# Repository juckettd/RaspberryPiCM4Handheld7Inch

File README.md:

# Raspberry Pi CM4 Handheld 7 - Aegis"

<p align="center"></p>

A repository for the Aegis, a 7" Raspberry Pi CM4 handheld device.

NOTE: This is still a work in progress. The design has been finalized but I'm still working on the instructions, therefore there might be steps that are missing at this moment.

## Summary

The Aegis is a DIY handheld that uses a 3D printed case with a Raspberry Pi CM4 and the official Raspberry Pi 7" screen. The official Raspberry Pi screen was chosen because it uses the DSI port on the Raspberry Pi and the CM4 could fit on either side of the display board. While a Raspberry Pi 4 might have fit inside the case, that was eventually designed, a custom carrier board was used to place the ports in the desired locations. To facilitate the controller portion of the device, the Wii U buttons and joysticks were used. This made it easy to use the button sub-assemblies so that the same tactile feel of the buttons could be maintained. The 3D printed case was based on the Wii U Gamepad but still designed from the ground up to fit the 7" screen and the custom circuit board. Finally, the whole thing was assembled with speakers and rumble motors to complete the handheld.

## Building the Handheld

To build the handheld you will need the items listed as required in the Bill of Materials along with the following tools:

Reflow Station or Reflow Oven<br/>
Solding Iron<br/>
Solder Paste<br/>
Tweezers<br/>
Small Philips Screw Driver<br/>
Small Flathead Screw Driver<br/>
Super Glue (preferrably CA glue with Accelerator)

There are items in the Bill of Materials that are listed as optional (such as the Wifi chip). These items are not required to get a working device but can be used if desired. At this time I will not provide directions on how to use the optional components so use at your discretion.

### Assembling the Circuit Board

The custom circuit boards are provided as eagle files in this repository. This includes the schematic, board layout, and the gerber files. 

To get the boards printed, a manufacturing facility is required. The website jlcpcb.com was used to print the 2 circuit board prototypes for the design. The larger of the two boards uses 4 layers, and the smaller one uses only 2 layers. It is recommended to also get the stencils with the boards so that applying the solder paste becomes much easier.

Once the boards have been received you will need to assemble the circuitry on the boards. This is done by getting all of the components provided in the bill of materials in the "PCB Components" sheet. Each item has a provided Link to where the item can be acquired along with the price at the time of the assembly of the prototype. After acquiring all of the components, use the stencil to apply solder paste to the circuit boards and then use tweezers to place each component. A reflow oven or reflow station should then be used to melt the solder paste and adhere the components. Lastly, any through hole components were then added on the using a soldering iron. 

Note: The teensy that is soldered to the board using the through holes. However, there are 4 pads that are located near the USB connector of the Teensy on the custom circuit board. They are the VBUS, D+, D-, and GND connections. I included the VBUS and GND connections as backups but they are not needed as the power and ground comes from the pins. But the D+, D- connections need to be connected to the teensy. On the underside of the teensy there are 4 pads that are in about the same location, a wire or some other form of connection is needed to connect the D+ from the teensy to the D+ on the custom circuit board, do the same with the D- connection.

While anyone who has experience with circuit boards will have their own method for assembling these boards I used the following steps and it is what I recommend for anyone without experience and a reflow oven (but a reflow station is required):
1. Using the stencil, put solder paste on the larger of the two boards on the side with a majority of the components
2. Place all of the surface mount components on that side of the board
3. Use a reflow station and heat the underside of the board until the solder paste on the top side melts to adhere the components. A tool to prop up the PCB comes in handy here. In my opinion this part is essential as some of the components are plastic and the hot air coming out of a reflow station can melt them.
4. Use a soldering iron to clean up an connections that didn't connect completely (You can watch youtube videos on how to do this, just search for solding iron and surface mount components)
5. Flip the board over and redo steps 1-4 for the underside of the board. Since these components are larger I just used the a soldering iron for all of the components, but the same procedure with the reflow station can be used. Just be careful with the hot air hitting components you have already put down, as they can fall off if the solder paste melts again.
6. Perform 1-5 for the second board and the few surface mount components that are on that board
7. Add all of the through hole items to both boards with a soldering iron (again youtube is your friend)

### Install Teensy Code

Before (or after) the circuit board has been assembled the teensy code needs to be pushed to the teensy. The teensy code is provided in the repo and you will need to follow the instructions on the teensy website for pushing code. Make sure that you set the board type to "XInput" otherwise it won't be seen as a XBox 360 Controller.

### 3D Printed Case

The files provided here and on Thingiverse are STL files for the case. They are printed in sections so that a printer with a standard bed size of 220mm x 220mm can be used print the case (I also provided the pieces combined for larger printers). Once they are printed they will have to be cleaned up and then glued together. Depending on which angle you choose to print the parts the cleanup step could be more or less cumbersome for the remove of support and getting good glue joints. I choose to print everything with flat surfaces on the bed to keep the post processing steps as easy as possible.

Once everything is glued together then no post processing is technically required to assemble the device. However, I chose to use filler, sand paper, and paint to get a really clean looking finish. The level of detail you desire on your handheld will be up to you based on how much effort you want to devote. Refer to youtube for how to sand and paint a 3D printed piece. However, try to keep the inside of the device as paint free as possible as the internal structure is already at the correct dimensions for the internal components.

I would also sand down the holes where the buttons will be located as they will to be rough from the 3D printing process. This can cause the buttons to stick.

Thingiverse link:
https://www.thingiverse.com/thing:4789405

### Assembly

Once the case and the PCB have been built and are ready to go the handheld can be assembled.

See the assembly instructions file provided with detailed instructions and pictures.

## Software

The carrier board was designed with the option of either using the CM4 lite or the CM4 with onboard memory. If the lite is used then a micro SD card is required. Follow the instructions on the official Raspberry Pi website or the RetroPie website to get the desired OS installed on the micro SD card. If the lite is not used then the internal memory can be loaded by removing the panel on the back of the handheld held and flipping the switch to the "ON" position. You can then use the micro USB port to load the CM4. Please refer to the official Raspberry Pi website on these steps. Once the OS is loaded then unplug the cable and flip the switch back to the off position.

### /boot/config.txt

Regardless of which CM4 you use and which method is used to load the OS, you will need to add the following lines to the /boot/config.txt file. These are also listed in the /Config/boot/config.txt file in this repository:

dtoverlay=dwc2,dr_mode=host<br/>
gpu_mem_256=128<br/>
gpu_mem_512=256<br/>
gpu_mem_1024=256<br/>
force_turbo=1<br/>
h264_freq=333

The lines above will optimize the graphics for Moonlight (if you choose to use it to stream PC games) and will enable USB 2.0 on the device to get the Teensy and external USB ports working.

### First Boot

For the first boot you will need to plug in a HDMI cord into the HDMI mini port. This is required since the screen won't work yet. Once it boots you need to connect to Wifi or Ethernet through whatever OS you have installed and run the following commands (also listed in the Config folder):

sudo apt install python3-gpiozero<br/>
sudo apt install python3-smbus<br/>
sudo wget https://goo.gl/iiVxuA -O /boot/dt-blob.bin

These will install required packages for a system monitor script and will also install the dt-blob.bin file to get the screen working. Once this is complete reboot the handheld and unplug the HDMI cord. The device will automatically switch to the screen on the reboot.

### System Setup

After the first boot and subsequent reboot you can either use git to download the items from the Config folder in this repository or you can copy the files to a USB stick and load them through the USB ports. Once on your Raspberry Pi, navigate to wherever you have loaded the files and run the setup.sh script as follows:

sudo bash ./setup.sh

This script will install files onto your Raspberry Pi to handle a series of things including:

Provide a startup script to detect when the HDMI cord is plugged in and switch to that output<br/>
Enable the buttons on the device to work<br/>
Enable sound through the speakers<br/>
Generating an overlay on the screen to give battery life, wifi status, bluetooth status, etc...<br/>
Provide a safe shut down proceedure for when the power button is pressed<br/>

Once the setup script is run the files you downloaded may be deleted.

## Have Fun

At this point the device should be fully up and running on whatever OS you decided to use. I suggest you start playing games and have fun :)

## Pictures/Videos

Images of the prototype are included if you want to see what a final version can look like and here is a list of youtube links for demoes on the device in operation:

Raspberry Pi CM4 Handheld - PC Games Demo
https://youtu.be/qqAcT7MvEfQ

Raspberry Pi CM4 Handheld - Pixel Desktop Logout
https://youtu.be/YUHz1qglbvk

Raspberry Pi CM4 Handheld - Touchscreen Demo
https://youtu.be/fQMbkvToMkI

Raspberry Pi CM4 Handheld - Youtube Video Showing Sound Quality
https://youtu.be/o1zs3FDNwGw

Raspberry Pi CM4 Handheld - Donkey Kong Country 2
https://youtu.be/sit6ItH9wHg

Raspberry Pi CM4 Handheld - Prototype Test
https://youtu.be/XAPKUmwa3sU

## Credits

To get the script and overlay down I took parts of the following work and adapted it to what I needed. But these projects deserve most of the credit for what they already did.

GBZ_Overlay 
https://github.com/d-rez/gbz_overlay

Pngview
https://github.com/AndrewFromMelbourne/raspidmx/tree/master/pngview

Safe shutdown script
https://github.com/crcerror/ES-generic-shutdown/blob/master/multi_switch.sh

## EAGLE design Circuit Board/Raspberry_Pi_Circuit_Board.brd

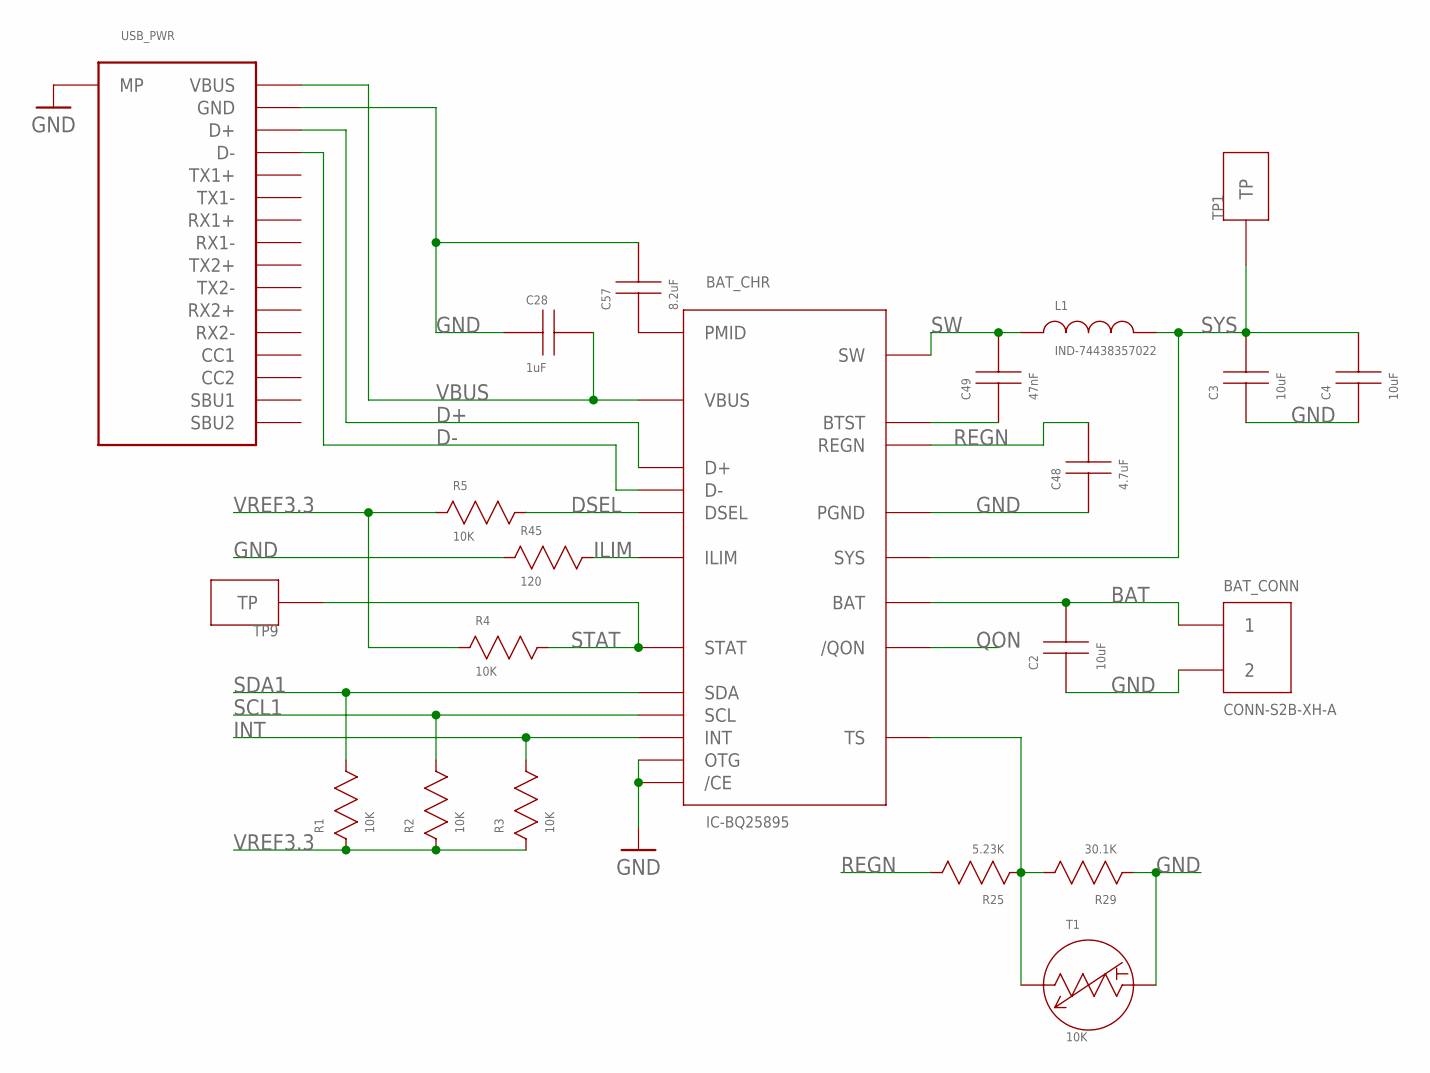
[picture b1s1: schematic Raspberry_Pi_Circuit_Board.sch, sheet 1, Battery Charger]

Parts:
BAT_CHR: IC-BQ25895
BAT_CONN: CONN-S2B-XH-A
C2, C3, C4: 10uF; CAP-603
C28: 1uF; CAP-603
C48: 4.7uF; CAP-603
C49: 47nF; CAP-603
C57: 8.2uF; CAP-603
L1: IND-74438357022
R1, R2, R3, R4, R5: 10K; RES-603
R25: 5.23K; RES-603
R29: 30.1K; RES-603
R45: 120; RES-603
T1: 10K; THERM-NTCLE101E3C90173
TP1, TP9: TESTPOINT
USB_PWR: USBC-USB-C31-S-RA-CS1D-BK-T/R

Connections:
BAT: BAT_CHR.BAT1 (BAT), BAT_CHR.BAT2 (BAT), BAT_CONN.1, C2.C; also elsewhere on the board
D+: BAT_CHR.D+, USB_PWR.D+, USB_PWR.D+_2 (D+)
D-: BAT_CHR.D-, USB_PWR.D-, USB_PWR.D-_2 (D-)
DSEL: BAT_CHR.DSEL, R5.C
GND: BAT_CHR./CE, BAT_CHR.OTG, BAT_CHR.PGND1 (PGND), BAT_CHR.PGND2 (PGND), BAT_CHR.PWRPAD (PGND), BAT_CONN.2, C2.A, C3.A, C4.A, C28.A, C48.A, C57.C, R29.A, R45.A, T1.2, USB_PWR.GND_1 (GND), USB_PWR.GND_2 (GND), USB_PWR.GND_3 (GND), USB_PWR.GND_4 (GND), USB_PWR.MP_1 (MP), USB_PWR.MP_2 (MP), USB_PWR.MP_3 (MP), USB_PWR.MP_4 (MP); also elsewhere on the board
ILIM: BAT_CHR.ILIM, R45.C
INT: BAT_CHR.INT, R3.C
unnamed: BAT_CHR.BTST, C49.A
unnamed: BAT_CHR.TS, R25.A, R29.C, T1.1
unnamed: BAT_CHR.PMID, C57.A
QON: BAT_CHR./QON; also elsewhere on the board
REGN: BAT_CHR.REGN, C48.C, R25.C
SCL1: BAT_CHR.SCL, R2.C; also elsewhere on the board
SDA1: BAT_CHR.SDA, R1.C; also elsewhere on the board
STAT: BAT_CHR.STAT, R4.C, TP9.TP; also elsewhere on the board
SW: BAT_CHR.SW1 (SW), BAT_CHR.SW2 (SW), C49.C, L1.A
SYS: BAT_CHR.SYS1 (SYS), BAT_CHR.SYS2 (SYS), C3.C, C4.C, L1.C, TP1.TP; also elsewhere on the board
VBUS: BAT_CHR.VBUS, C28.C, USB_PWR.VBUS_1 (VBUS), USB_PWR.VBUS_2 (VBUS), USB_PWR.VBUS_3 (VBUS), USB_PWR.VBUS_4 (VBUS)
VREF3.3: R1.A, R2.A, R3.A, R4.A, R5.A; also elsewhere on the board

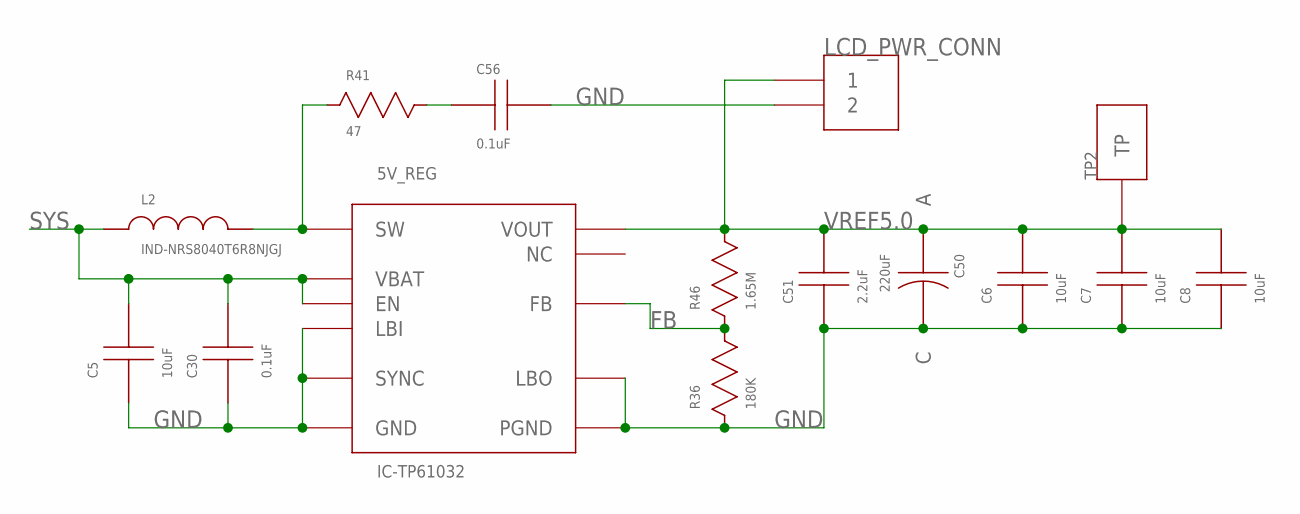
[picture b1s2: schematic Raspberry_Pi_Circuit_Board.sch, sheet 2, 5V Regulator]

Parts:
5V_REG: IC-TP61032; IC-TPS61032
C5, C6, C7, C8: 10uF; CAP-603
C30, C56: 0.1uF; CAP-603
C50: 220uF; CAP-TAN-1411
C51: 2.2uF; CAP-603
L2: IND-NRS8040T6R8NJGJ
LCD_PWR_CONN: CONN-282834-2
R36: 180K; RES-603
R41: 47; RES-603
R46: 1.65M; RES-603
TP2: TESTPOINT

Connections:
FB: 5V_REG.FB, R36.C, R46.A
GND: 5V_REG.GND, 5V_REG.LBI, 5V_REG.LBO, 5V_REG.PGND1 (PGND), 5V_REG.PGND2 (PGND), 5V_REG.PGND3 (PGND), 5V_REG.PWRPAD (PGND), 5V_REG.SYNC, C5.A, C6.A, C7.A, C8.A, C30.A, C50.C, C51.A, C56.C, LCD_PWR_CONN.2, R36.A; also elsewhere on the board
unnamed: C56.A, R41.C
SNUB: 5V_REG.SW1 (SW), 5V_REG.SW2 (SW), L2.C, R41.A
SYS: 5V_REG.EN, 5V_REG.VBAT, C5.C, C30.C, L2.A; also elsewhere on the board
VREF5.0: 5V_REG.VOUT1 (VOUT), 5V_REG.VOUT2 (VOUT), 5V_REG.VOUT3 (VOUT), C6.C, C7.C, C8.C, C50.A, C51.C, LCD_PWR_CONN.1, R46.C, TP2.TP; also elsewhere on the board

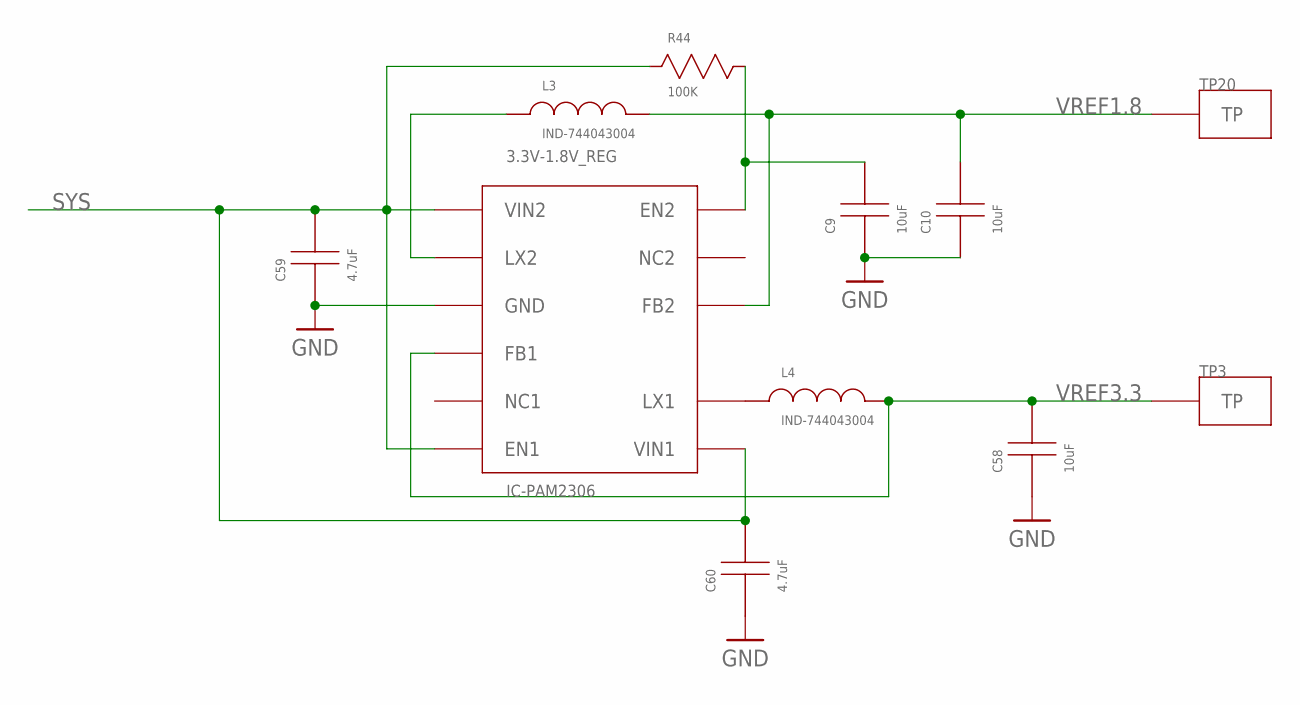
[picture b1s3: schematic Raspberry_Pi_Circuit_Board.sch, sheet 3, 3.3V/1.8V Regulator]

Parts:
3.3V-1.8V_REG: IC-PAM2306
C9, C10, C58: 10uF; CAP-603
C59, C60: 4.7uF; CAP-603
L3, L4: IND-744043004
R44: 100K; RES-603
TP3, TP20: TESTPOINT

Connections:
GND: 3.3V-1.8V_REG.GND1 (GND), 3.3V-1.8V_REG.GND2 (GND), 3.3V-1.8V_REG.PWRPAD (GND), C9.A, C10.A, C58.A, C59.A, C60.A; also elsewhere on the board
unnamed: 3.3V-1.8V_REG.LX2, L3.A
unnamed: 3.3V-1.8V_REG.EN2, C9.C, R44.C
unnamed: 3.3V-1.8V_REG.LX1, L4.A
SYS: 3.3V-1.8V_REG.EN1, 3.3V-1.8V_REG.VIN1, 3.3V-1.8V_REG.VIN2, C59.C, C60.C, R44.A; also elsewhere on the board
VREF1.8: 3.3V-1.8V_REG.FB2, C10.C, L3.C, TP20.TP; also elsewhere on the board
VREF3.3: 3.3V-1.8V_REG.FB1, C58.C, L4.C, TP3.TP; also elsewhere on the board

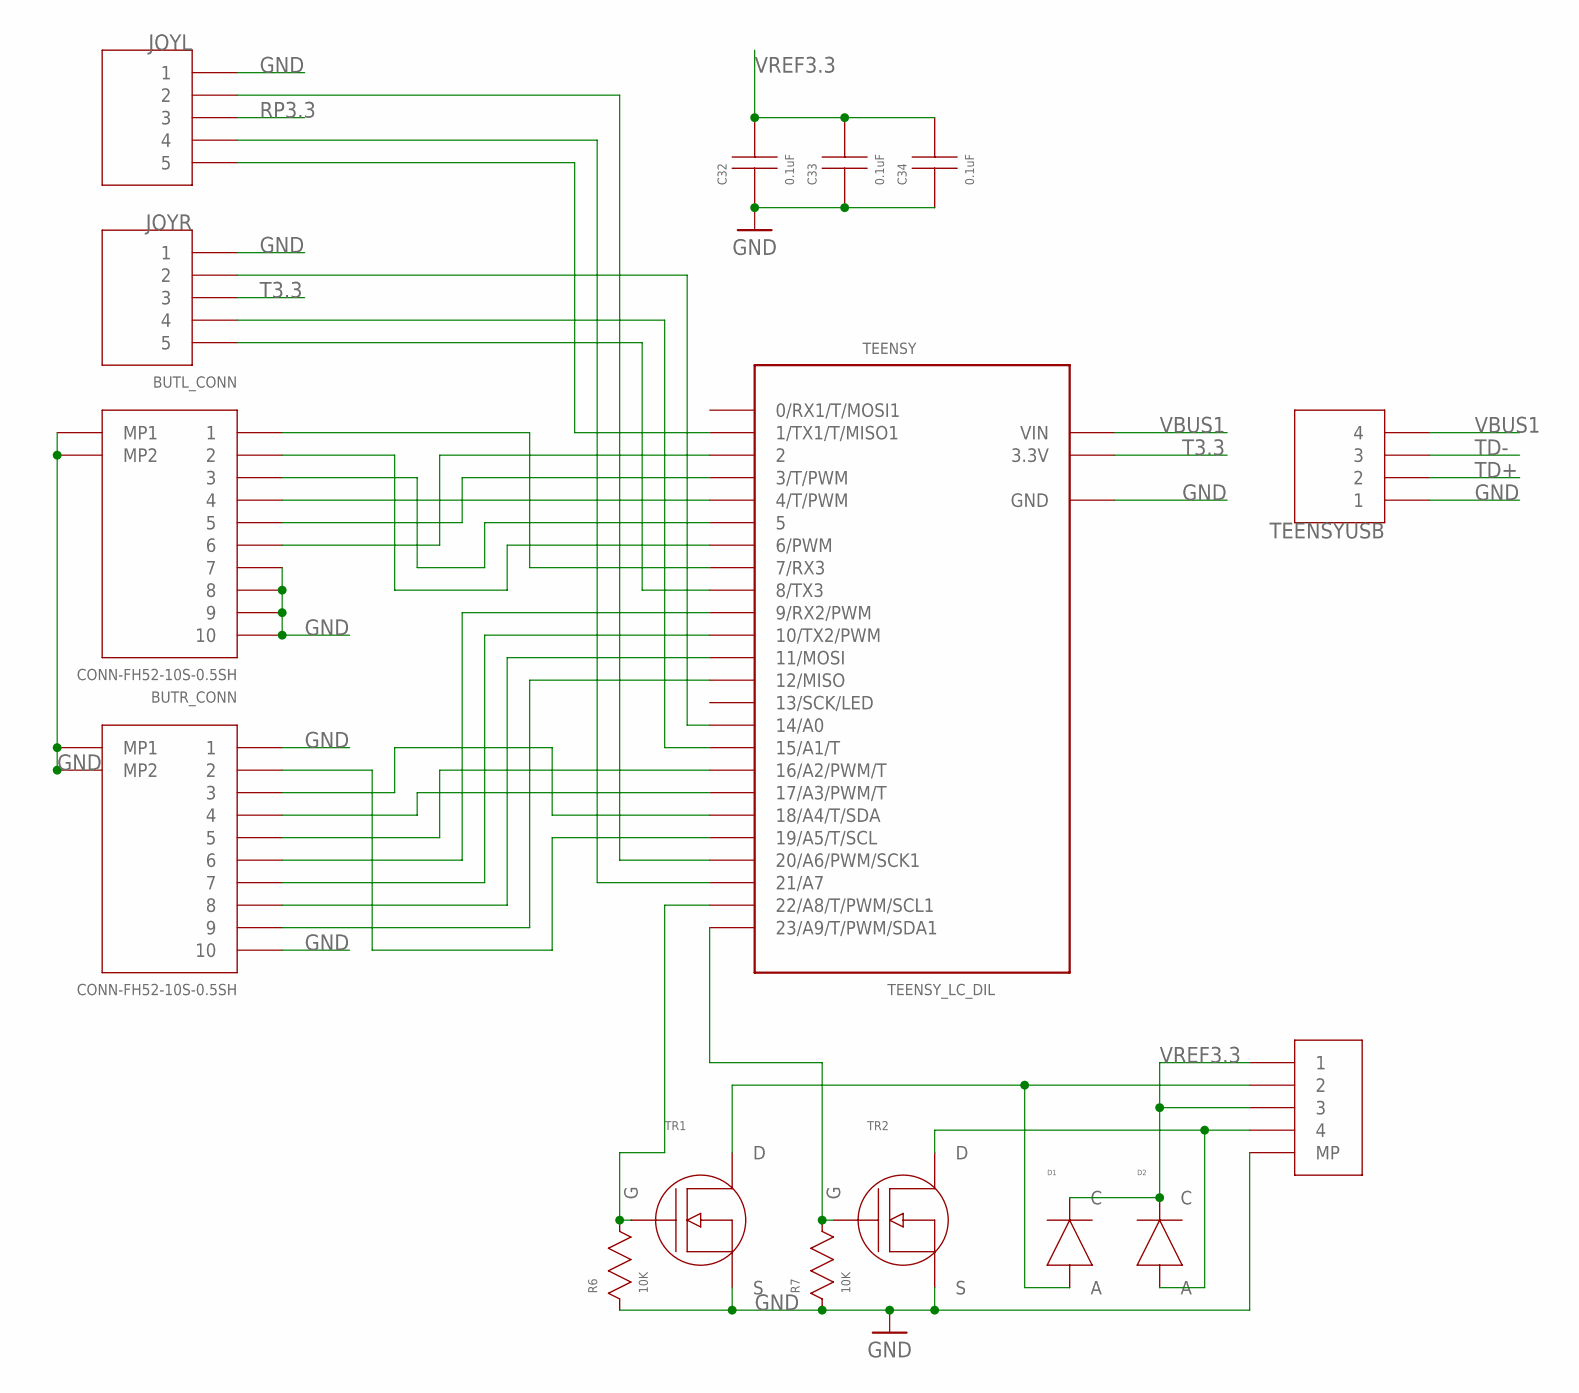
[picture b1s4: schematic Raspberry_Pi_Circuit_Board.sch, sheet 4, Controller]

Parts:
BUTL_CONN: CONN-FH52-10S-0.5SH
BUTR_CONN: CONN-FH52-10S-0.5SH
C32, C33, C34: 0.1uF; CAP-603
D1, D2: DIODE-X3-WLB1608-2
JOYL: CONN_5PIN
JOYR: CONN_5PIN
MOT_CONN: CONN-VS4B-ZR-SM4A-TF
R6, R7: 10K; RES-603
TEENSY: TEENSY_LC_DIL; TEENSY_3.0-3.2&LC_DIL
TEENSYUSB: CONN_4PIN
TR1, TR2: TRAN-DMG2302UKQ

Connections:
GND: BUTL_CONN.7, BUTL_CONN.8, BUTL_CONN.9, BUTL_CONN.10, BUTL_CONN.MP1, BUTL_CONN.MP2, BUTR_CONN.1, BUTR_CONN.10, BUTR_CONN.MP1, BUTR_CONN.MP2, C32.A, C33.A, C34.A, JOYL.1, JOYR.1, MOT_CONN.MP_1 (MP), MOT_CONN.MP_2 (MP), R6.A, R7.A, TEENSY.AGND (GND), TEENSY.GND, TEENSYUSB.1, TR1.S, TR2.S; also elsewhere on the board
unnamed: JOYR.2, TEENSY.14/A0
unnamed: JOYR.4, TEENSY.15/A1 (15/A1/T)
unnamed: R6.C, TEENSY.22/A8 (22/A8/T/PWM/SCL1), TR1.G
unnamed: R7.C, TEENSY.23/A9 (23/A9/T/PWM/SDA1), TR2.G
unnamed: BUTR_CONN.8, TEENSY.11 (11/MOSI)
unnamed: D2.A, MOT_CONN.4, TR2.D
unnamed: D1.A, MOT_CONN.2, TR1.D
unnamed: BUTR_CONN.9, TEENSY.12 (12/MISO)
unnamed: BUTR_CONN.7, TEENSY.10 (10/TX2/PWM)
unnamed: BUTR_CONN.6, TEENSY.9 (9/RX2/PWM)
unnamed: JOYR.5, TEENSY.8 (8/TX3)
unnamed: BUTR_CONN.5, TEENSY.16/A2 (16/A2/PWM/T)
unnamed: BUTR_CONN.4, TEENSY.17/A3 (17/A3/PWM/T)
unnamed: BUTR_CONN.3, TEENSY.18/A4 (18/A4/T/SDA)
unnamed: BUTR_CONN.2, TEENSY.19/A5 (19/A5/T/SCL)
unnamed: JOYL.2, TEENSY.20/A6 (20/A6/PWM/SCK1)
unnamed: JOYL.4, TEENSY.21/A7
unnamed: JOYL.5, TEENSY.1 (1/TX1/T/MISO1)
unnamed: BUTL_CONN.6, TEENSY.2
unnamed: BUTL_CONN.5, TEENSY.3 (3/T/PWM)
unnamed: BUTL_CONN.4, TEENSY.4 (4/T/PWM)
unnamed: BUTL_CONN.3, TEENSY.5
unnamed: BUTL_CONN.2, TEENSY.6 (6/PWM)
unnamed: BUTL_CONN.1, TEENSY.7 (7/RX3)
RP3.3: JOYL.3; also elsewhere on the board
T3.3: JOYR.3, TEENSY.3.3V
TD+: TEENSYUSB.2; also elsewhere on the board
TD-: TEENSYUSB.3; also elsewhere on the board
VBUS1: TEENSY.VIN, TEENSYUSB.4; also elsewhere on the board
VREF3.3: C32.C, C33.C, C34.C, D1.C, D2.C, MOT_CONN.1, MOT_CONN.3; also elsewhere on the board

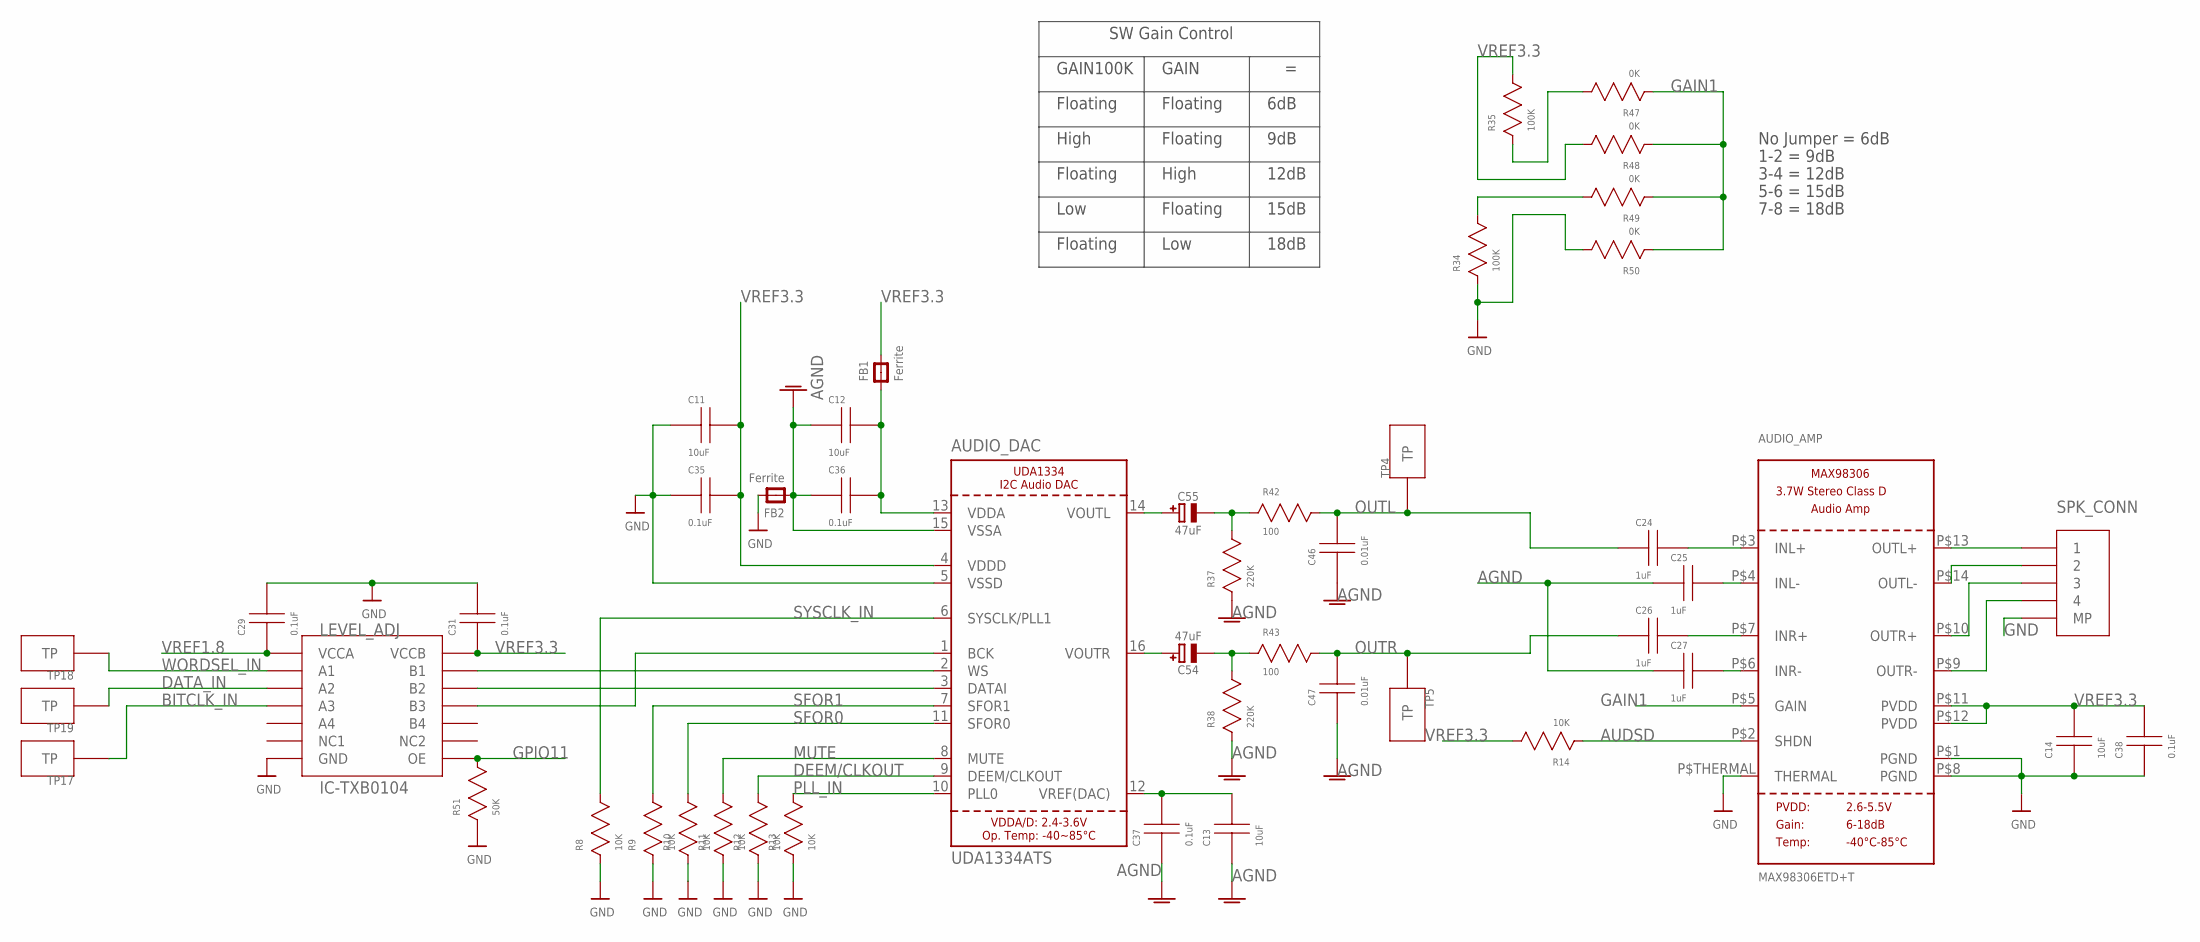
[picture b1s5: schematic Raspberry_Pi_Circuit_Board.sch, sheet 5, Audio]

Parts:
AUDIO_AMP: MAX98306ETD+T; TDFN14_3X3MM
AUDIO_DAC: UDA1334ATS; SSOP16_4.4MM
C11, C12, C13, C14: 10uF; CAP-603
C24, C25, C26, C27: 1uF; CAP-603
C29, C31, C35, C36, C37, C38: 0.1uF; CAP-603
C46, C47: 0.01uF; CAP-603
C54, C55: 47uF; PANASONIC_C
FB1, FB2: Ferrite; 0805@1
LEVEL_ADJ: IC-TXB0104
R8, R9, R10, R11, R12, R13, R14: 10K; RES-603
R34, R35: 100K; RES-603
R37, R38: 220K; RES-603
R42, R43: 100; RES-603
R47, R48, R49, R50: 0K; RES-603
R51: 50K; RES-603
SPK_CONN: CONN-VS4B-ZR-SM4A-TF
TP4, TP5, TP17, TP18, TP19: TESTPOINT

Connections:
AGND: AUDIO_DAC.15 (VSSA), C12.A, C13.A, C25.A, C27.A, C36.A, C37.A, C46.A, C47.A, FB2.1, R37.A, R38.A; also elsewhere on the board
AUDSD: AUDIO_AMP.P$2 (SHDN), R14.A; also elsewhere on the board
BITCLK_IN: LEVEL_ADJ.A3, TP17.TP; also elsewhere on the board
DATA_IN: LEVEL_ADJ.A2, TP19.TP; also elsewhere on the board
DEEM/CLKOUT: AUDIO_DAC.9 (DEEM/CLKOUT), R12.C
GAIN1: AUDIO_AMP.P$5 (GAIN), R47.A, R48.A, R49.A, R50.A
GND: AUDIO_AMP.P$1 (PGND), AUDIO_AMP.P$8 (PGND), AUDIO_AMP.P$THERMAL (THERMAL), AUDIO_DAC.5 (VSSD), C11.A, C14.A, C29.C, C31.C, C35.A, C38.A, FB2.2, LEVEL_ADJ.GND, R8.A, R9.A, R10.A, R11.A, R12.A, R13.A, R34.A, R50.C, R51.A, SPK_CONN.MP_1 (MP), SPK_CONN.MP_2 (MP); also elsewhere on the board
GPIO11: LEVEL_ADJ.OE, R51.C; also elsewhere on the board
MUTE: AUDIO_DAC.8 (MUTE), R11.C
unnamed: AUDIO_DAC.13 (VDDA), C12.C, C36.C, FB1.1
unnamed: C54.-, R38.C, R43.A
unnamed: C55.-, R37.C, R42.A
unnamed: AUDIO_DAC.1 (BCK), LEVEL_ADJ.B3
unnamed: AUDIO_DAC.2 (WS), LEVEL_ADJ.B1
unnamed: AUDIO_DAC.12 (VREF(DAC)), C13.C, C37.C
unnamed: AUDIO_DAC.16 (VOUTR), C54.+
unnamed: AUDIO_DAC.14 (VOUTL), C55.+
unnamed: R35.A, R47.C
unnamed: R34.C, R49.C
unnamed: AUDIO_AMP.P$3 (INL+), C24.C
unnamed: AUDIO_AMP.P$4 (INL-), C25.C
unnamed: AUDIO_AMP.P$7 (INR+), C26.C
unnamed: AUDIO_AMP.P$6 (INR-), C27.C
unnamed: AUDIO_AMP.P$13 (OUTL+), SPK_CONN.1
unnamed: AUDIO_AMP.P$14 (OUTL-), SPK_CONN.2
unnamed: AUDIO_AMP.P$10 (OUTR+), SPK_CONN.3
unnamed: AUDIO_AMP.P$9 (OUTR-), SPK_CONN.4
unnamed: AUDIO_DAC.3 (DATAI), LEVEL_ADJ.B2
OUTL: C24.A, C46.C, R42.C, TP4.TP; also elsewhere on the board
OUTR: C26.A, C47.C, R43.C, TP5.TP; also elsewhere on the board
PLL_IN: AUDIO_DAC.10 (PLL0), R13.C
SFOR0: AUDIO_DAC.11 (SFOR0), R10.C
SFOR1: AUDIO_DAC.7 (SFOR1), R9.C
SYSCLK_IN: AUDIO_DAC.6 (SYSCLK/PLL1), R8.C
VREF1.8: C29.A, LEVEL_ADJ.VCCA; also elsewhere on the board
VREF3.3: AUDIO_AMP.P$11 (PVDD), AUDIO_AMP.P$12 (PVDD), AUDIO_DAC.4 (VDDD), C11.C, C14.C, C31.A, C35.C, C38.C, FB1.2, LEVEL_ADJ.VCCB, R14.C, R35.C, R48.C; also elsewhere on the board
WORDSEL_IN: LEVEL_ADJ.A1, TP18.TP; also elsewhere on the board

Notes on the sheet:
GAIN100K
GAIN
Floating
6dB
High
9dB
12dB
Low
15dB
18dB
SW Gain Control
No Jumper = 6dB
1-2 = 9dB
3-4 = 12dB
5-6 = 15dB
7-8 = 18dB

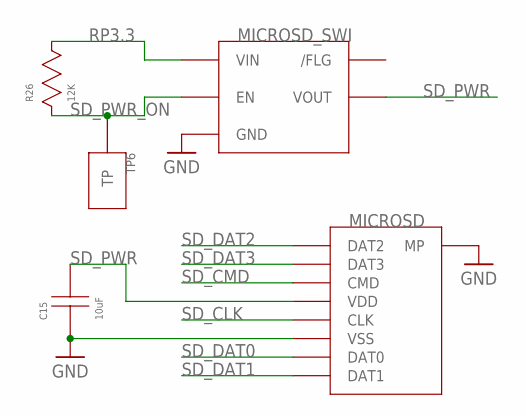
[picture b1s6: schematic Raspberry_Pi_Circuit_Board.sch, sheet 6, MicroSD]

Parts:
C15: 10uF; CAP-603
MICROSD: MICROSD-5033981892_SD
MICROSD_SWI: IC-RT9742
R26: 12K; RES-603
TP6: TESTPOINT

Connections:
GND: C15.A, MICROSD.DL (MP), MICROSD.DS (MP), MICROSD.MP_1 (MP), MICROSD.MP_2 (MP), MICROSD.MP_3 (MP), MICROSD.MP_4 (MP), MICROSD.VSS, MICROSD_SWI.GND; also elsewhere on the board
RP3.3: MICROSD_SWI.VIN, R26.C; also elsewhere on the board
SD_CLK: MICROSD.CLK; also elsewhere on the board
SD_CMD: MICROSD.CMD; also elsewhere on the board
SD_DAT0: MICROSD.DAT0; also elsewhere on the board
SD_DAT1: MICROSD.DAT1; also elsewhere on the board
SD_DAT2: MICROSD.DAT2; also elsewhere on the board
SD_DAT3: MICROSD.DAT3; also elsewhere on the board
SD_PWR: C15.C, MICROSD.VDD, MICROSD_SWI.VOUT
SD_PWR_ON: MICROSD_SWI.EN, R26.A, TP6.TP; also elsewhere on the board

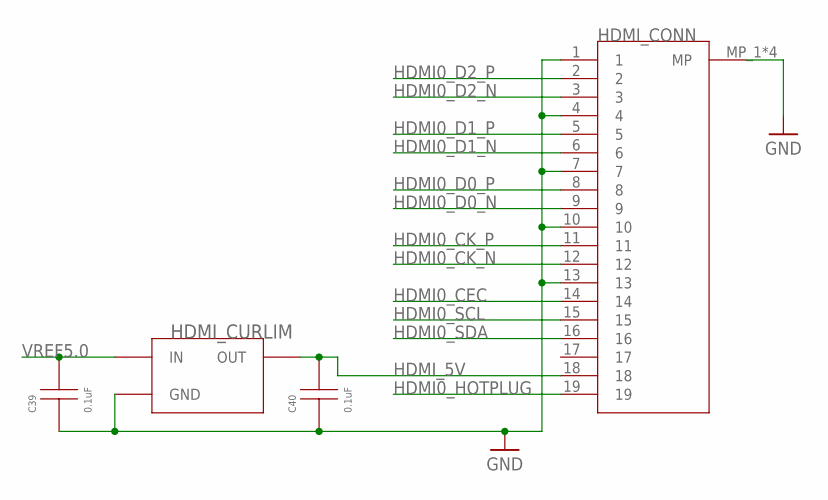
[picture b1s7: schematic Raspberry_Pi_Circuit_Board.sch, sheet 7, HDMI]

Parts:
C39, C40: 0.1uF; CAP-603
HDMI_CONN: HDMI-2001-1-2-21-00-BK
HDMI_CURLIM: CURLIM-AP2331

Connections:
GND: C39.A, C40.A, HDMI_CONN.1, HDMI_CONN.4, HDMI_CONN.7, HDMI_CONN.10, HDMI_CONN.13, HDMI_CONN.MP_1 (MP), HDMI_CONN.MP_2 (MP), HDMI_CONN.MP_3 (MP), HDMI_CONN.MP_4 (MP), HDMI_CURLIM.GND; also elsewhere on the board
HDMI0_CEC: HDMI_CONN.14; also elsewhere on the board
HDMI0_CK_N: HDMI_CONN.12; also elsewhere on the board
HDMI0_CK_P: HDMI_CONN.11; also elsewhere on the board
HDMI0_D0_N: HDMI_CONN.9; also elsewhere on the board
HDMI0_D0_P: HDMI_CONN.8; also elsewhere on the board
HDMI0_D1_N: HDMI_CONN.6; also elsewhere on the board
HDMI0_D1_P: HDMI_CONN.5; also elsewhere on the board
HDMI0_D2_N: HDMI_CONN.3; also elsewhere on the board
HDMI0_D2_P: HDMI_CONN.2; also elsewhere on the board
HDMI0_HOTPLUG: HDMI_CONN.19; also elsewhere on the board
HDMI0_SCL: HDMI_CONN.15; also elsewhere on the board
HDMI0_SDA: HDMI_CONN.16; also elsewhere on the board
HDMI_5V: C40.C, HDMI_CONN.18, HDMI_CURLIM.OUT
VREF5.0: C39.C, HDMI_CURLIM.IN; also elsewhere on the board

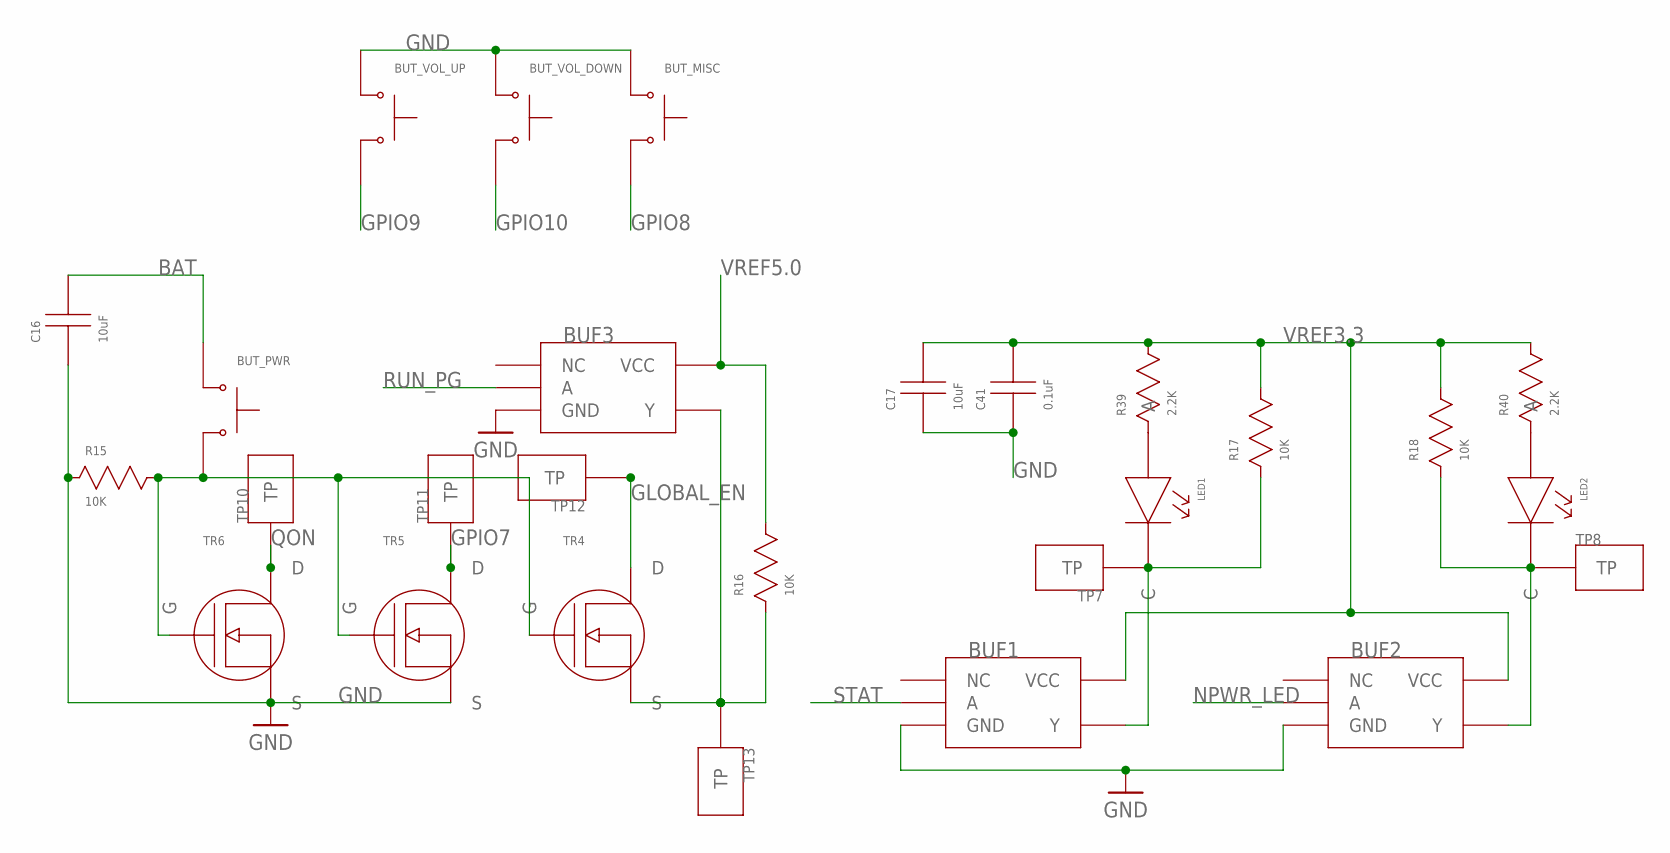
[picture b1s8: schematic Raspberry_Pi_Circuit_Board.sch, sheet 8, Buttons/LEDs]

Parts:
BUF1, BUF2, BUF3: BUF-74LVC1G07
BUT_MISC: BUT-KSS331GLFS
BUT_PWR: BUT-KSS331GLFS
BUT_VOL_DOWN: BUT-KSS331GLFS
BUT_VOL_UP: BUT-KSS331GLFS
C16, C17: 10uF; CAP-603
C41: 0.1uF; CAP-603
LED1, LED2: LED-SM0805UWC
R15, R16, R17, R18: 10K; RES-603
R39, R40: 2.2K; RES-603
TP7, TP8, TP10, TP11, TP12, TP13: TESTPOINT
TR4, TR5, TR6: TRAN-DMG2302UKQ

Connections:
BAT: BUT_PWR.1, C16.C; also elsewhere on the board
GLOBAL_EN: TP12.TP, TR4.D; also elsewhere on the board
GND: BUF1.GND, BUF2.GND, BUF3.GND, BUT_MISC.1, BUT_VOL_DOWN.1, BUT_VOL_UP.1, C16.A, C17.A, C41.A, R15.A, TR5.S, TR6.S; also elsewhere on the board
GPIO7: TP11.TP, TR5.D; also elsewhere on the board
GPIO8: BUT_MISC.2; also elsewhere on the board
GPIO9: BUT_VOL_UP.2; also elsewhere on the board
GPIO10: BUT_VOL_DOWN.2; also elsewhere on the board
unnamed: BUF1.Y, LED1.C, R17.A, TP7.TP
unnamed: BUT_PWR.2, R15.C, TR4.G, TR5.G, TR6.G
unnamed: LED1.A, R39.A
unnamed: LED2.A, R40.A
unnamed: BUF2.Y, LED2.C, R18.A, TP8.TP
unnamed: BUF3.Y, R16.A, TP13.TP, TR4.S
NPWR_LED: BUF2.A; also elsewhere on the board
QON: TP10.TP, TR6.D; also elsewhere on the board
RUN_PG: BUF3.A; also elsewhere on the board
STAT: BUF1.A; also elsewhere on the board
VREF3.3: BUF1.VCC, BUF2.VCC, C17.C, C41.C, R17.C, R18.C, R39.C, R40.C; also elsewhere on the board
VREF5.0: BUF3.VCC, R16.C; also elsewhere on the board

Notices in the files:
parts and their libraries:
microbuilder: This work is placed in the public domain, and may be freely used for commercial and non-commercial work with the following conditions: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
